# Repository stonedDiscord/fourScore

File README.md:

This is a pretty much exact clone of the NES 4-Score adapter (PAL version)

I did this nondestructively by scanning the bottom of the board and tracing the board.
There is no scan of the top side because there are no traces on it and i'd have to desolder the controller ports, potentionally wrecking them.

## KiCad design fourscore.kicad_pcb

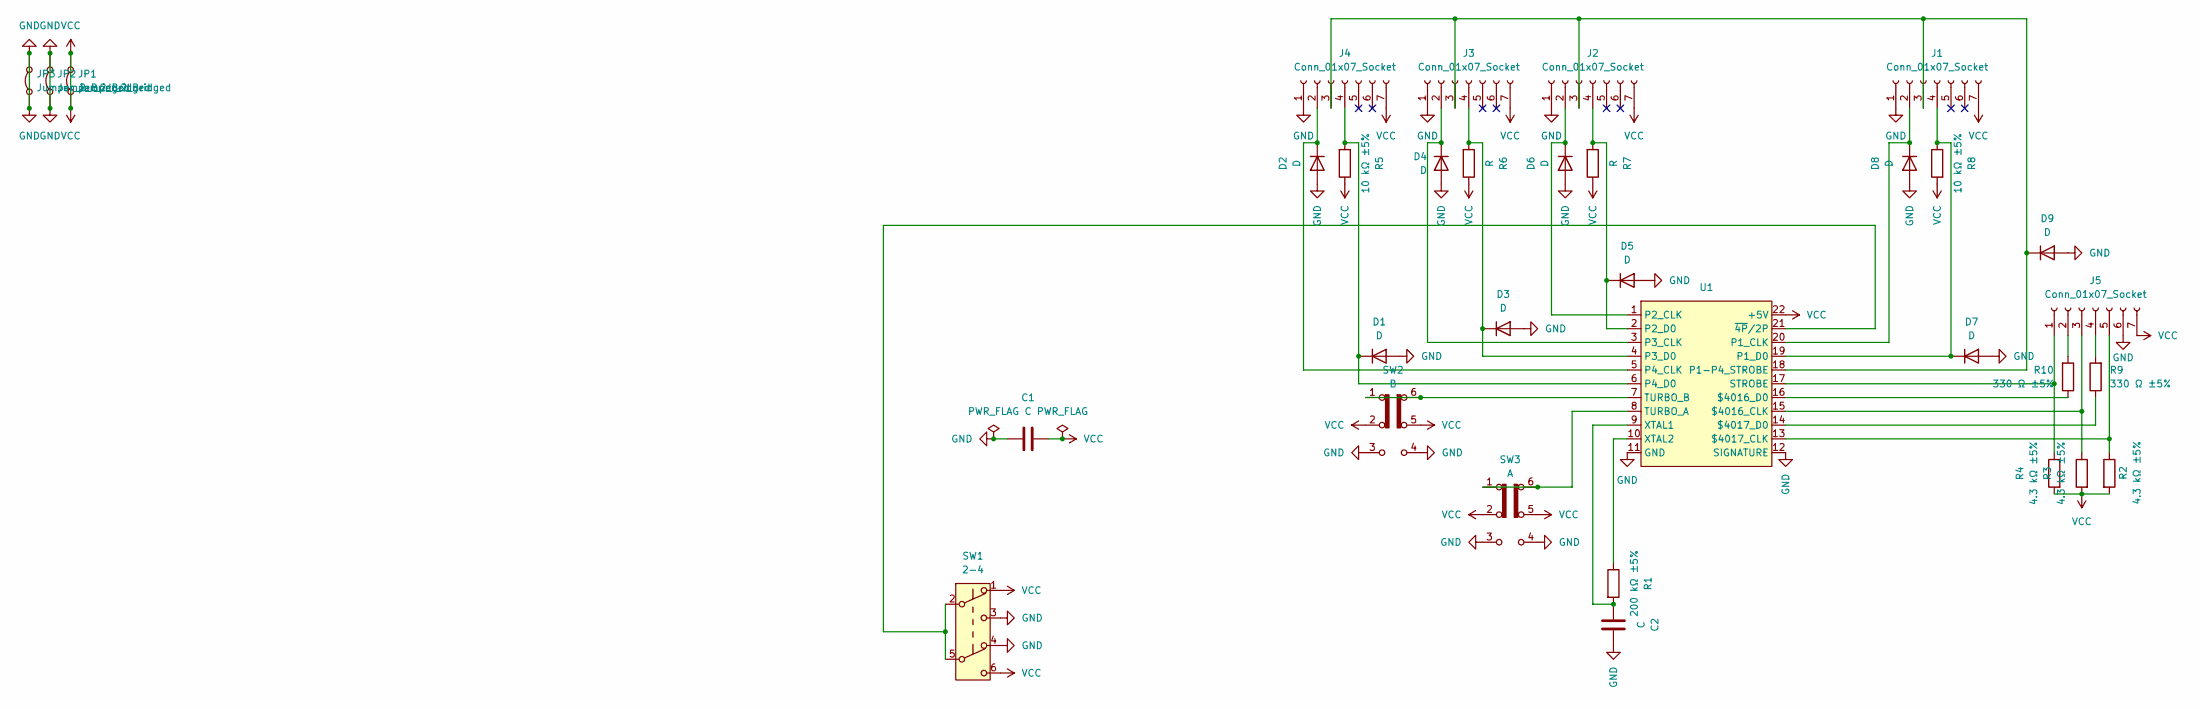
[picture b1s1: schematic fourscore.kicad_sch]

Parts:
C1: C; C_Axial_L3.8mm_D2.6mm_P7.50mm_Horizontal
C2: C; C_Rect_L9.0mm_W2.5mm_P7.50mm_MKT
D1, D2, D3, D4, D5, D6, D7, D8, D9: D; D_DO-34_SOD68_P7.62mm_Horizontal
J1, J2, J3, J4: Conn_01x07_Socket; Controller
J5: Conn_01x07_Socket; PinHeader_1x07_P2.54mm_Vertical
JP1, JP2, JP3: Jumper_2_Bridged; R_Axial_DIN0204_L3.6mm_D1.6mm_P7.62mm_Horizontal
R1: 200 kΩ ±5%; R_Axial_DIN0204_L3.6mm_D1.6mm_P7.62mm_Horizontal
R2, R3, R4: 4.3 kΩ ±5%; R_Axial_DIN0204_L3.6mm_D1.6mm_P7.62mm_Horizontal
R5, R8: 10 kΩ ±5%; R_Axial_DIN0204_L3.6mm_D1.6mm_P7.62mm_Horizontal
R6, R7: R; R_Axial_DIN0204_L3.6mm_D1.6mm_P7.62mm_Horizontal
R9, R10: 330 Ω ±5%; R_Axial_DIN0204_L3.6mm_D1.6mm_P7.62mm_Horizontal
SW1: 2-4; SW_CK_JS202011CQN_DPDT_Straight
SW2: B; SW_Push_2P2T_Toggle_CK_PVA2OAH5xxxxxxV2
SW3: A; SW_Push_2P2T_Toggle_CK_PVA2OAH5xxxxxxV2
U1: DIP-22_W10.16mm

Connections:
GND: C1.1, C2.2, D1.2 (A), D2.2 (A), D3.2 (A), D4.2 (A), D5.2 (A), D6.2 (A), D7.2 (A), D8.2 (A), D9.2 (A), J1.1, J2.1, J3.1, J4.1, J5.6, JP2.1 (A), JP2.2 (B), JP3.1 (A), JP3.2 (B), SW1.3 (C), SW1.4 (A), SW2.3 (C), SW2.4 (A), SW3.3 (C), SW3.4 (A), U1.11 (GND), U1.12 (SIGNATURE)
unnamed: D1.1 (K), J4.4, R5.2, U1.6 (P4_D0)
unnamed: D2.1 (K), J4.2, U1.5 (P4_CLK)
unnamed: D3.1 (K), J3.4, R6.2, U1.4 (P3_D0)
unnamed: D4.1 (K), J3.2, U1.3 (P3_CLK)
unnamed: D5.1 (K), J2.4, R7.2, U1.2 (P2_D0)
unnamed: D6.1 (K), J2.2, U1.1 (P2_CLK)
unnamed: D7.1 (K), J1.4, R8.1, U1.19 (P1_D0)
unnamed: D8.1 (K), J1.2, U1.20 (P1_CLK)
unnamed: D9.1 (K), J1.3, J2.3, J3.3, J4.3, U1.18 (P1-P4_STROBE)
unnamed: J5.1, R4.1, U1.17 (STROBE)
unnamed: J5.2, R10.2
unnamed: J5.3, R3.1, U1.15 ($4016_CLK)
unnamed: J5.4, R9.2
unnamed: J5.5, R2.1, U1.13 ($4017_CLK)
unnamed: R10.1, U1.16 ($4016_D0)
unnamed: R9.1, U1.14 ($4017_D0)
unnamed: SW3.1 (A), SW3.6 (C), U1.8 (TURBO_A)
unnamed: SW2.1 (A), SW2.6 (C), U1.7 (TURBO_B)
unnamed: C2.1, R1.2, U1.9 (XTAL1)
unnamed: R1.1, U1.10 (XTAL2)
unnamed: SW1.2 (B), SW1.5 (B), U1.21 (~4P/2P)
VCC: C1.2, J1.7, J2.7, J3.7, J4.7, J5.7, JP1.1 (A), JP1.2 (B), R2.2, R3.2, R4.2, R5.1, R6.1, R7.1, R8.2, SW1.1 (A), SW1.6 (C), SW2.2 (B), SW2.5 (B), SW3.2 (B), SW3.5 (B), U1.22 (+5V)

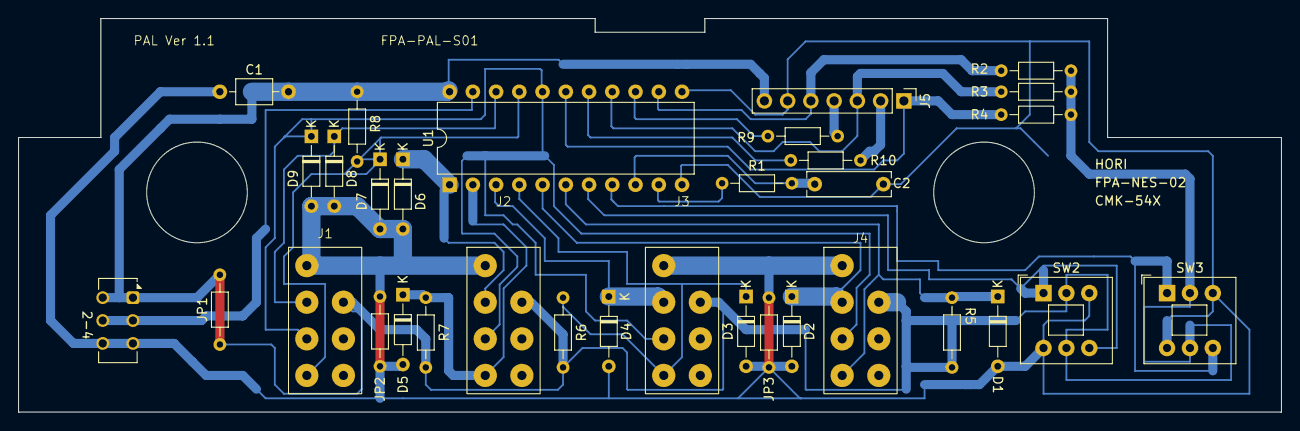
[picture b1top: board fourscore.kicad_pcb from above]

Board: 2 copper layers, 138.0 x 43.0 mm, 33 parts (0 on the bottom side), 23 nets.

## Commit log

2024-04-08 files
2024-08-12 dealt with all warnings
2024-08-12 add readme
2025-05-02 linguist override
